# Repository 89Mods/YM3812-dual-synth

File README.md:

# YM3812-dual-synth
MIDI synthesizer built from two YM3812s for 18-voice mono or 9-voice stereo. More info: https://tholin.dev/ym3812d/

# Build instructions

## PCB

The gerber file for the synthesizer can be found [here](https://github.com/89Mods/YM3812-dual-synth/tree/main/KiCad/production) and you should be able to use this with all the major board houses. Just make sure they correctly recognize it as a 4-layer PCB. The dimensions of the PCB are low enough to where it should be cheap despite it being 4-layers (8€ on JLCPCB).

## Parts

The YM3812s and their DACs are the most annoying parts to obtain. They can be easily found on eBay and AliExpress by simply using "YM3812" and "Y3014" keywords, but the condition of the parts can vary. The AliExpress listings I bought from are [here](https://de.aliexpress.com/item/1005001723547967.html) and [here.](https://de.aliexpress.com/item/1005002637379806.html)

The nanoCH32V003 mini dev board you can maybe even find at your favorite maker shop, but also [on AliExpress](https://de.aliexpress.com/item/1005005221751705.html). If there is an option to buy the board plus a "WCHLinkE" you may use that (recommended), but I will also show you how to use an Arduino Uno to flash the synthesizer firmware later on (though this requires a Linux install or WSL).

All the other integrated circuits can be found at various electronics retailers:

LM358: [TME](https://www.tme.eu/de/details/lm358ap/tht-operationsverstarker/texas-instruments/) - [Mouser](https://www.mouser.de/ProductDetail/Texas-Instruments/LM358N-NOPB?qs=QbsRYf82W3GXbWt%2FvwDTcQ%3D%3D) - [LCSC](https://www.lcsc.com/product-detail/Operational-Amplifier_HGSEMI-LM358N_C434570.html)

6N139 (or 6N138): [TME](https://www.tme.eu/de/details/6n139-eve/optokoppler-analogausgang/everlight/6n139/) - [Mouser](https://www.mouser.de/ProductDetail/Vishay-Semiconductors/6N139?qs=WHRYDAs2thAk3qh0MF5UBQ%3D%3D) - [LCSC](https://www.lcsc.com/product-detail/Optocouplers-Logic-Output_CT-Micro-International-6N139_C191869.html)

SN74LV1T34DBVRG4: [TME](https://www.tme.eu/de/details/sn74lv1t34dbvrg4/logische-wandler/texas-instruments/) - [Mouser](https://www.mouser.de/ProductDetail/Texas-Instruments/SN74LV1T34DBVRG4?qs=vdi0iO8H4N10R%252Bt%252BjmxZrg%3D%3D) - [LCSC](https://www.lcsc.com/product-detail/Buffer-Driver-Transceiver_Texas-Instruments-SN74LV1T34DBVR_C100024.html)

MX25L1005 (or MX25L2006 or 25Q32 or any spiflash that supports the 25xx command set and is made by Winbond or Macronix): [TME](https://www.tme.eu/de/details/mx25l2006em1i-12g/serielle-flash-speicher/macronix-international/mx25l2006em1i-12g-tube/) - [LCSC](https://www.lcsc.com/product-detail/NOR-FLASH_MXIC-Macronix-MX25L2006EM1I-12G_C135940.html) - I also recommend looking for "MX25L1005" on AliExpress, you can get them really cheap there.

74HCT164 (or 74LS164, NOT 74HC164): [TME](https://www.tme.eu/de/details/cd74hct164e/schieberegister/texas-instruments/) - [Mouser](https://www.mouser.de/ProductDetail/Texas-Instruments/SN74LS164NE4?qs=SL3LIuy2dWzMustM9SNFlQ%3D%3D) - [LCSC](https://www.lcsc.com/product-detail/Shifting-Register_Texas-Instruments-SN74LS164N_C129807.html)

## Build notes

The BOM for assembling the board is available [here](https://example.com/). Otherwise, there is little special to keep in mind, just solder the SMD components first, and use pin sockets for the nanoCH. It needs to be removed from the synthesizer to be re-flashed.

The 5-pin header at the bottom of the board is where MIDI input is. You will need to wire in a broken-out MIDI connector here. Only two need to actually be wired up. The 2nd pin from the left wires to the Current Sink on the MIDI connector and the 4th pin from the left to Current Source.

## Flashing Firmware

This step changes depending on if you’re running Windows or Linux, and if you have bought the WCHLinkE. In any case, you will need the minichlink utility.

If you are running Linux, it is part of a repo [here](https://github.com/cnlohr/ch32v003fun/tree/master/minichlink) and can be built using the makefile there. Also read the readme there for instructions on installing the required udev rules.

If you are running windows, download the pre-built executable files [here](https://github.com/cnlohr/ch32v003fun/blob/master/minichlink/minichlink.exe) and [here](https://github.com/cnlohr/ch32v003fun/blob/master/minichlink/libusb-1.0.dll) (you need both files).

A pre-built binary of the synthesizer’s firmware is [here](https://github.com/89Mods/YM3812-dual-synth/blob/main/RV_Firmware/synth.bin). To use a WCH-LinkE to flash it, wire up the single-wire IO pin of the programmer (labeled "SWDIO" or similar) to the SWIO pin of the nanoCH (the middle of the three-pin header on the back). To then use it to flash the firmware file, the command-line `minichlink(.exe) -w synth.bin flash -b` should work on either OS, and you are already done.

If you did not buy the WCHLinkE, but have an Arduino Uno laying around, you can use Ardulink. It is available on its own repo [here](https://gitlab.com/BlueSyncLine/arduino-ch32v003-swio). Follow the instructions there to set it up. Note that it requires a Linux install or WSL to build, but can be *used* from either OS.
Additionally, the repo mentions connecting the nanoCH’s power to an Arduino pin, but I’ve found that to be really unstable and it still works fine with the nanoCH powered continuously. You only need to wire up SWIO to the Arduino (its the middle pin of the three-pin header on top).

On Windows: `minichlink.exe -c COMx -w synth.bin flash -b` where "COMx" needs to be substituted with whichever COM port your Arduino uses.

On Linux: `minichlink -c /dev/ttyACMx -w synth.bin flash -b` where "ttyACMx" needs to be substituted with whichever tty port your Arduino uses.

## Uploading patches

A set of patches for all standard MIDI instruments must be uploaded to the synthesizer at least once. A public-domain file containing patches is included in this repo: [GENMIDI.op2](https://github.com/89Mods/YM3812-dual-synth/blob/main/PatchUploader/GENMIDI.op2). You can edit this to your liking using the [OPL3 Bank Editor](https://github.com/Wohlstand/OPL3BankEditor) (scroll down and use one of the "Fresh dev builds", the latest GitHub release is years old and has issues).

A custom tool I made can then be used to send this data to the synthesizer over the MIDI port. [PatchUploader.jar](https://github.com/89Mods/YM3812-dual-synth/blob/main/PatchUploader/PatchUploader.jar) (requires Java 11 or higher). If your system does not already associate .jar files with Java, you may need to run it through a command line with `java -jar PatchUploader.jar`

The UI should be straight forward. After selecting the the .op2 file and the MIDI port of the synthesizer, click the upload button and you should see activity on the synthesizer in the form of a flashing blue LED on the nanoCH. It should flash multiple times and the synth should then reset and play a jingle. If nothing happens, check if the MIDI port is wired up correctly and if any software or hardware in your setup is potentially blocking the sysex messages used by the uploader.

The uploader software releases the MIDI port when it is done, meaning you can keep it open and use it multiple times by just clicking the button again. The file is also re-loaded each time and does not need to be selected again.

## Switching Modes

The synthesizer can operate in three distinct modes.

**Mono**: both sound chips are combined into a single output. This allows their voices to be used together, 18 in total. This is the most basic and default mode.

**Stereo**: every note is played on both chips simultaniously, but its volume on either chip is adjusted according to the MIDI channel’s stereo pan, giving the illusion of stereo audio. This, however, reduced the amount of usable voices back to 9.

**Independent**: each chip acts as a separate synthesizer. Each responds only to events on a specific range of MIDI channels and their outputs can be individually obtained on the same output as the stereo audio.

MIDI sysex messages are used to switch between these. The codes are as follows:

Switch to Mono: `0xF0 0x7E 0x56 0x72 0xF7`

Switch to Stereo: `0xF0 0x7E 0x56 0x76 0xF7`

Switch to Independent: `0xF0 0x7E 0x56 0x75 0xF7`

By default, the synthesizer listens to all channels in Mono and Stereo modes and in Independent mode, channels 1 - 8 will go to the first chip and 9 - 16 to the second. An alternative firmware image is available [here](https://github.com/89Mods/YM3812-dual-synth/blob/main/RV_Firmware/synth_alt.bin) where the synthesizer only listens to channel 15 in Mono and Stereo and in Independent, channel 14 goes to the first and channel 15 to the second chip.

To fully customize this behavior, you will need to build the firmware yourself, after editing `synth.c` and changing the values in the `accepted_channels` array for Mono and Stereo and `accepted_channels_first` and `accepted_channels_second` for Independent. These are right at the beginning of the file and are just lists of MIDI channels (warning: 0-indexed).

## Building the firmware from source

If you want to build the firmware from source, it has do be done on a native Linux install, or in Windows Subsystem for Linux. You will need to install the [RISC-V GNU Toolchain](https://github.com/riscv-collab/riscv-gnu-toolchain) first, though this step varies between distros. I recommend cloning the repo and building it from source, as that is what worked for me.

Then, clone this repo and execute the script to set up the environment: `sh clone_subrepos_and_patch.sh`

Then, you can enter the RV_Firmware directory and use the makefile there. Simply `make` will both build the firmware and then flash the output using minichlink.

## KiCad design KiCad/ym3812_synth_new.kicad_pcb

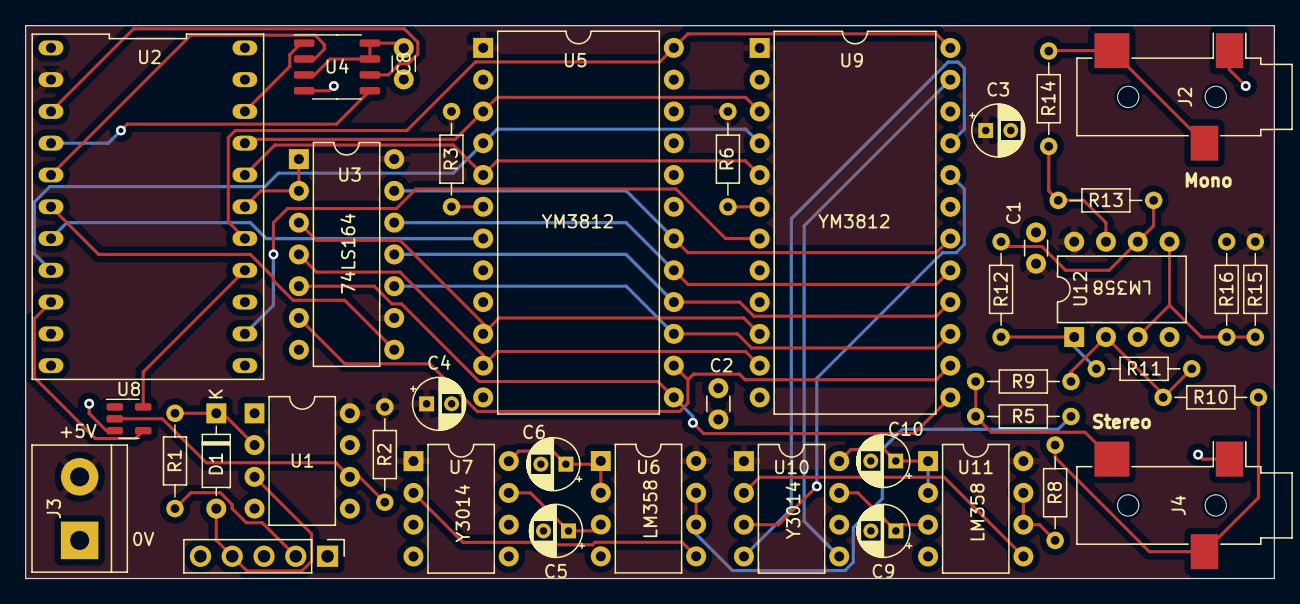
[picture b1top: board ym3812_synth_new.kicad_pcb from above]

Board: 4 copper layers, 99.8 x 44.2 mm, 40 parts (0 on the bottom side), 52 nets.

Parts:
C1, C2, C8: 100nF; C_Disc_D3.0mm_W1.6mm_P2.50mm
C3, C4, C5, C6, C9, C10: 10µF; CP_Radial_D4.0mm_P2.00mm
D1: 1N4148; D_DO-35_SOD27_P7.62mm_Horizontal
J1: DIN-5; PinHeader_1x05_P2.54mm_Vertical
J2, J4: AudioJack3; Jack_3.5mm_CUI_SJ-3523-SMT_Horizontal
J3: Screw_Terminal_01x02; TerminalBlock_bornier-2_P5.08mm
R1, R2, R3, R6: 220; R_Axial_DIN0204_L3.6mm_D1.6mm_P7.62mm_Horizontal
R5, R8, R14: 1K; R_Axial_DIN0204_L3.6mm_D1.6mm_P7.62mm_Horizontal
R9, R10, R11, R12, R13: 100K; R_Axial_DIN0204_L3.6mm_D1.6mm_P7.62mm_Horizontal
R15, R16: 10K; R_Axial_DIN0204_L3.6mm_D1.6mm_P7.62mm_Horizontal
U1: 6N139; DIP-8_W7.62mm
U2: nanoCH32V003; DIP-22_610_ELL
U3: 74HCT164; DIP-14_W7.62mm
U4: MX25L1005; SOP-8_3.9x4.9mm_P1.27mm
U5, U9: YM3812; DIP-24_W15.24mm
U6, U11, U12: LM358; DIP-8_W7.62mm
U7, U10: Y3014; DIP-8_W7.62mm
U8: SN74LV1T34DCK; SOT-23-5

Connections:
4MHz: U2.16 (D0), U5.24 (φM), U9.24 (φM)
+3.3V: C8.1, U2.15 (3V3), U4.3 (~WP), U4.7 (~HOLD), U4.8 (Vcc), U8.5 (VCC)
+5V: C1.1, C2.1, C3.1, C4.1, J3.2, R2.2, R3.2, R6.2, R15.1, U1.8 (VCC), U2.2 (5V), U3.9 (~MR), U3.14 (VCC), U5.1 (Vss), U6.8 (V+), U7.1 (Vcc), U9.1 (Vss), U10.1 (Vcc), U11.8 (V+), U12.8 (V+)
A0: U2.8 (D4), U5.4 (A0), U9.4 (A0)
GND: C1.2, C2.2, C3.2, C4.2, C5.2, C6.2, C8.2, C9.2, C10.2, J2.S, J3.1, J4.S, R16.2, U1.5 (GND), U2.1 (GND), U2.22 (GND), U3.7 (GND), U4.4 (GND), U5.12 (GND), U6.4 (V-), U7.6 (GND), U8.3 (GND), U9.12 (GND), U10.6 (GND), U11.4 (V-), U12.4 (V-)
unnamed: D1.2 (A), J1.4, U1.3 (C2)
unnamed: D1.1 (K), R1.2, U1.2 (C1)
unnamed: J1.2, R1.1
unnamed: J2.R, J2.T, R14.1
unnamed: R11.1, R12.2, U12.1
unnamed: R13.1, R14.2, U12.7
unnamed: R2.1, U1.6 (VO2), U8.2 (A)
unnamed: U2.17 (C0), U3.1 (DSA), U3.2 (DSB)
unnamed: U2.6 (D2), U3.8 (CP)
unnamed: U2.9 (D5), U8.4 (Y)
unnamed: U5.21 (MO), U7.4 (SD)
unnamed: U5.20 (SH), U7.3 (LD)
unnamed: R3.1, U5.6 (~RD)
unnamed: U5.23 (φSY), U7.5 (CLK)
unnamed: C5.1, U6.3 (+), U7.7 (RB)
unnamed: C6.1, U6.1, U6.2 (-), U7.8 (MP)
unnamed: U6.5 (+), U7.2 (Out)
unnamed: R5.2, U6.6 (-), U6.7
unnamed: R6.1, U9.6 (~RD)
unnamed: U9.23 (φSY), U10.5 (CLK)
unnamed: U9.20 (SH), U10.3 (LD)
unnamed: C10.1, U10.8 (MP), U11.1, U11.2 (-)
unnamed: U10.2 (Out), U11.5 (+)
unnamed: C9.1, U10.7 (RB), U11.3 (+)
unnamed: U9.21 (MO), U10.4 (SD)
unnamed: R8.2, U11.6 (-), U11.7
unnamed: R15.2, R16.1, U12.3 (+), U12.5 (+)
unnamed: R9.1, R10.1, R11.2, U12.2 (-)
unnamed: R12.1, R13.2, U12.6 (-)
Q0: U3.3 (Q0), U5.10 (D0), U9.10 (D0)
Q1: U3.4 (Q1), U5.11 (D1), U9.11 (D1)
Q2: U3.5 (Q2), U5.13 (D2), U9.13 (D2)
Q3: U3.6 (Q3), U5.14 (D3), U9.14 (D3)
Q4: U3.10 (Q4), U5.15 (D4), U9.15 (D4)
Q5: U3.11 (Q5), U5.16 (D5), U9.16 (D5)
Q6: U3.12 (Q6), U5.17 (D6), U9.17 (D6)
Q7: U3.13 (Q7), U5.18 (D7), U9.18 (D7)
S1: J4.T, R5.1, R9.2
S2: J4.R, R8.1, R10.2
SCLK: U2.3 (C5), U4.6 (SCLK)
SI: U2.5 (C7), U4.2 (SO)
SO: U2.4 (C6), U4.5 (SI)
~CS1: U2.7 (D3), U5.7 (~CS)
~CS2: U2.13 (A1), U9.7 (~CS)
~CS: U2.20 (C3), U4.1 (~CS)
~IC: U2.19 (C2), U5.3 (~IC), U9.3 (~IC)
~WR: U2.18 (C1), U5.5 (~WR), U9.5 (~WR)

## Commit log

2024-02-01 Add existing files.
2024-02-15 Gerber file
2024-02-15 Pre-built firmware images.
2024-03-10 Bug fixes related to mode switching.
2025-05-10 Update to compile with newer ch32fun
2026-04-06 Update code to work with newer ch32fun.
